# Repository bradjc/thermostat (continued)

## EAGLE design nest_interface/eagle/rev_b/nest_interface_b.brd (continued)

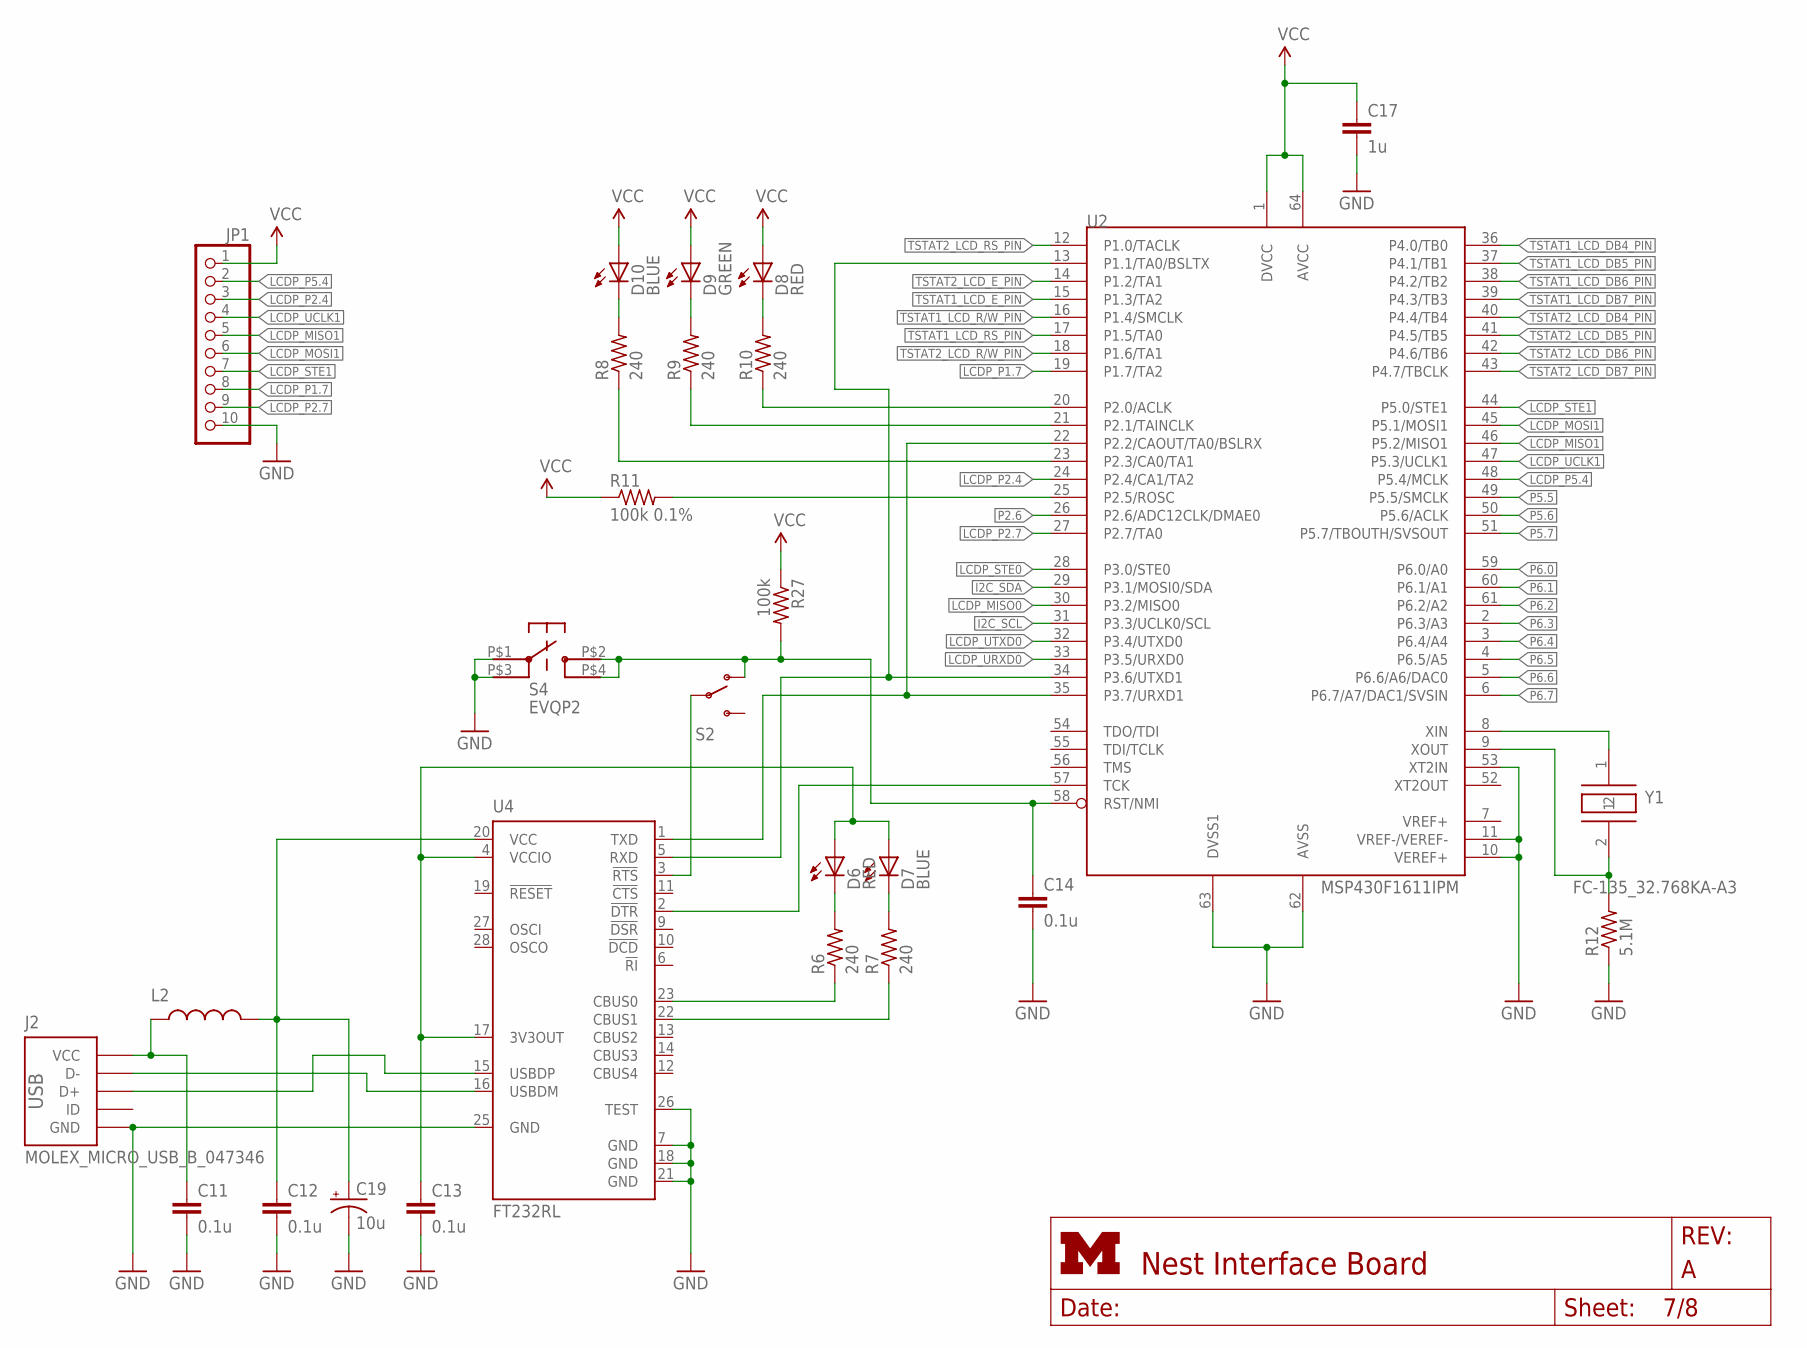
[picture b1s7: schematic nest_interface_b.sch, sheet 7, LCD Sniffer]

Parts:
C11, C12, C13, C14: 0.1u; C0603
C17: 1u; C0603
C19: 10u; EIA3216; DIGIKEY 478-1655-1-ND
D6, D8: RED; LED-0603
D7, D10: BLUE; LED-0603
D9: GREEN; LED-0603
J2: MOLEX_MICRO_USB_B_047346
JP1: PINHD-1X10; 1X10
L2: INDUCTOR0603; 0603; DIGIKEY 240-2373-1-ND
R6, R7, R8, R9, R10: 240; R0603
R11: 100k 0.1%; R0603
R12: 5.1M; R0603
R27: 100k; R0603
S2: SWITCH-SPSTPTH; SWITCH-SPDT; DIGIKEY EG1903-ND
S4: EVQP2; DIGIKEY P11084SCT-ND
U2: MSP430F1611IPM; PM/PAG64
U4: FT232RL; SSOP28; DIGIKEY 768-1007-1-ND
Y1: FC-135_32.768KA-A3; FC-135; DIGIKEY 535-9543-1-ND

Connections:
GND: C11.2, C12.2, C13.2, C14.2, C17.2, C19.C (-), J2.GND, JP1.10, R12.1, S4.P$1, S4.P$3, U2.10 (VEREF+), U2.11 (VREF-/VEREF-), U2.53 (XT2IN), U2.62 (AVSS), U2.63 (DVSS1), U4.7 (GND), U4.18 (GND), U4.21 (GND), U4.25 (GND), U4.26 (TEST); also elsewhere on the board
I2C_SCL: U2.31 (P3.3/UCLK0/SCL); also elsewhere on the board
I2C_SDA: U2.29 (P3.1/MOSI0/SDA); also elsewhere on the board
LCDP_MISO0: U2.30 (P3.2/MISO0)
LCDP_MISO1: JP1.5, U2.46 (P5.2/MISO1)
LCDP_MOSI1: JP1.6, U2.45 (P5.1/MOSI1)
LCDP_P1.7: JP1.8, U2.19 (P1.7/TA2)
LCDP_P2.3: R8.1, U2.23 (P2.3/CA0/TA1)
LCDP_P2.4: JP1.3, U2.24 (P2.4/CA1/TA2)
LCDP_P2.7: JP1.9, U2.27 (P2.7/TA0)
LCDP_P5.4: JP1.2, U2.48 (P5.4/MCLK)
LCDP_STE0: U2.28 (P3.0/STE0)
LCDP_STE1: JP1.7, U2.44 (P5.0/STE1)
LCDP_UART1RX: U2.22 (P2.2/CAOUT/TA0/BSLRX), U2.35 (P3.7/URXD1), U4.1 (TXD)
LCDP_UART1TX: U2.13 (P1.1/TA0/BSLTX), U2.34 (P3.6/UTXD1), U4.5 (RXD)
LCDP_UCLK1: JP1.4, U2.47 (P5.3/UCLK1)
LCDP_URXD0: U2.33 (P3.5/URXD0)
LCDP_UTXD0: U2.32 (P3.4/UTXD0)
unnamed: R10.1, U2.20 (P2.0/ACLK)
unnamed: D8.C, R10.2
unnamed: U2.8 (XIN), Y1.1
unnamed: C11.1, J2.VCC, L2.1
unnamed: J2.D-, U4.16 (USBDM)
unnamed: J2.D+, U4.15 (USBDP)
unnamed: C12.1, C19.A (+), L2.2, U4.20 (VCC)
unnamed: R6.1, U4.23 (CBUS0)
unnamed: R7.1, U4.22 (CBUS1)
unnamed: D6.C, R6.2
unnamed: D7.C, R7.2
unnamed: U2.57 (TCK), U4.2 (!DTR)
unnamed: C13.1, D6.A, D7.A, U4.4 (VCCIO), U4.17 (3V3OUT)
unnamed: R12.2, U2.9 (XOUT), Y1.2
unnamed: D9.C, R9.2
unnamed: R11.2, U2.25 (P2.5/ROSC)
unnamed: D10.C, R8.2
unnamed: R9.1, U2.21 (P2.1/TAINCLK)
P2.6: U2.26 (P2.6/ADC12CLK/DMAE0)
P5.5: U2.49 (P5.5/SMCLK)
P5.6: U2.50 (P5.6/ACLK)
P5.7: U2.51 (P5.7/TBOUTH/SVSOUT)
P6.0: U2.59 (P6.0/A0)
P6.1: U2.60 (P6.1/A1)
P6.2: U2.61 (P6.2/A2)
P6.3: U2.2 (P6.3/A3)
P6.4: U2.3 (P6.4/A4)
P6.5: U2.4 (P6.5/A5)
P6.6: U2.5 (P6.6/A6/DAC0)
P6.7: U2.6 (P6.7/A7/DAC1/SVSIN)
RST1: C14.1, R27.2, S2.1 (O), S4.P$2, S4.P$4, U2.58 (RST/NMI)
RST_USB1: S2.2, U4.3 (!RTS)
TSTAT1_LCD_DB4_PIN: U2.36 (P4.0/TB0); also elsewhere on the board
TSTAT1_LCD_DB5_PIN: U2.37 (P4.1/TB1); also elsewhere on the board
TSTAT1_LCD_DB6_PIN: U2.38 (P4.2/TB2); also elsewhere on the board
TSTAT1_LCD_DB7_PIN: U2.39 (P4.3/TB3); also elsewhere on the board
TSTAT1_LCD_E_PIN: U2.15 (P1.3/TA2); also elsewhere on the board
TSTAT1_LCD_R/W_PIN: U2.16 (P1.4/SMCLK); also elsewhere on the board
TSTAT1_LCD_RS_PIN: U2.17 (P1.5/TA0); also elsewhere on the board
TSTAT2_LCD_DB4_PIN: U2.40 (P4.4/TB4); also elsewhere on the board
TSTAT2_LCD_DB5_PIN: U2.41 (P4.5/TB5); also elsewhere on the board
TSTAT2_LCD_DB6_PIN: U2.42 (P4.6/TB6); also elsewhere on the board
TSTAT2_LCD_DB7_PIN: U2.43 (P4.7/TBCLK); also elsewhere on the board
TSTAT2_LCD_E_PIN: U2.14 (P1.2/TA1); also elsewhere on the board
TSTAT2_LCD_R/W_PIN: U2.18 (P1.6/TA1); also elsewhere on the board
TSTAT2_LCD_RS_PIN: U2.12 (P1.0/TACLK); also elsewhere on the board
VCC: C17.1, D8.A, D9.A, D10.A, JP1.1, R11.1, R27.1, U2.1 (DVCC), U2.64 (AVCC); also elsewhere on the board

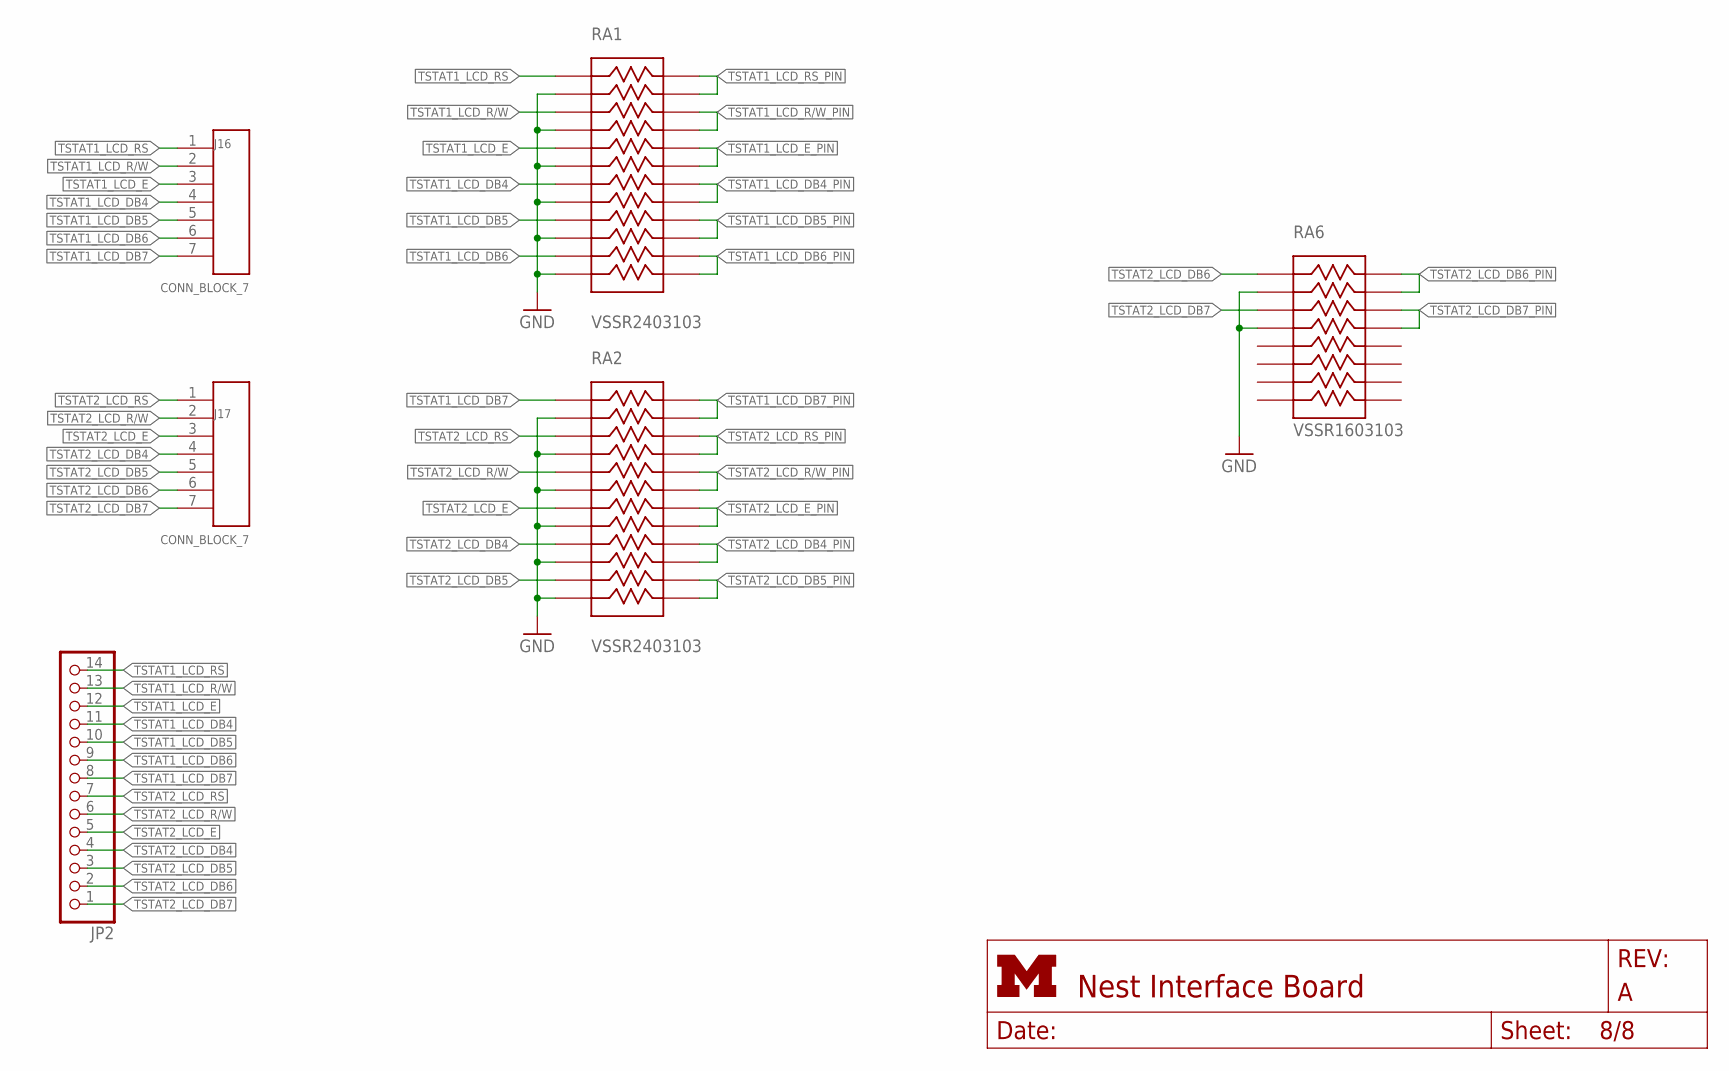
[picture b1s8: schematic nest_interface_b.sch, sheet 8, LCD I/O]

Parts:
J16, J17: CONN_BLOCK_7
JP2: PINHD-1X14; 1X14
RA1, RA2: VSSR2403103; LSSOP-24
RA6: VSSR1603103; LSSOP-16

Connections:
GND: RA1.2, RA1.4, RA1.6, RA1.8, RA1.10, RA1.12, RA2.2, RA2.4, RA2.6, RA2.8, RA2.10, RA2.12, RA6.2, RA6.4; also elsewhere on the board
TSTAT1_LCD_DB4: J16.4, JP2.11, RA1.7
TSTAT1_LCD_DB4_PIN: RA1.17, RA1.18; also elsewhere on the board
TSTAT1_LCD_DB5: J16.5, JP2.10, RA1.9
TSTAT1_LCD_DB5_PIN: RA1.15, RA1.16; also elsewhere on the board
TSTAT1_LCD_DB6: J16.6, JP2.9, RA1.11
TSTAT1_LCD_DB6_PIN: RA1.13, RA1.14; also elsewhere on the board
TSTAT1_LCD_DB7: J16.7, JP2.8, RA2.1
TSTAT1_LCD_DB7_PIN: RA2.23, RA2.24; also elsewhere on the board
TSTAT1_LCD_E: J16.3, JP2.12, RA1.5
TSTAT1_LCD_E_PIN: RA1.19, RA1.20; also elsewhere on the board
TSTAT1_LCD_R/W: J16.2, JP2.13, RA1.3
TSTAT1_LCD_R/W_PIN: RA1.21, RA1.22; also elsewhere on the board
TSTAT1_LCD_RS: J16.1, JP2.14, RA1.1
TSTAT1_LCD_RS_PIN: RA1.23, RA1.24; also elsewhere on the board
TSTAT2_LCD_DB4: J17.4, JP2.4, RA2.9
TSTAT2_LCD_DB4_PIN: RA2.15, RA2.16; also elsewhere on the board
TSTAT2_LCD_DB5: J17.5, JP2.3, RA2.11
TSTAT2_LCD_DB5_PIN: RA2.13, RA2.14; also elsewhere on the board
TSTAT2_LCD_DB6: J17.6, JP2.2, RA6.1
TSTAT2_LCD_DB6_PIN: RA6.15, RA6.16; also elsewhere on the board
TSTAT2_LCD_DB7: J17.7, JP2.1, RA6.3
TSTAT2_LCD_DB7_PIN: RA6.13, RA6.14; also elsewhere on the board
TSTAT2_LCD_E: J17.3, JP2.5, RA2.7
TSTAT2_LCD_E_PIN: RA2.17, RA2.18; also elsewhere on the board
TSTAT2_LCD_R/W: J17.2, JP2.6, RA2.5
TSTAT2_LCD_R/W_PIN: RA2.19, RA2.20; also elsewhere on the board
TSTAT2_LCD_RS: J17.1, JP2.7, RA2.3
TSTAT2_LCD_RS_PIN: RA2.21, RA2.22; also elsewhere on the board

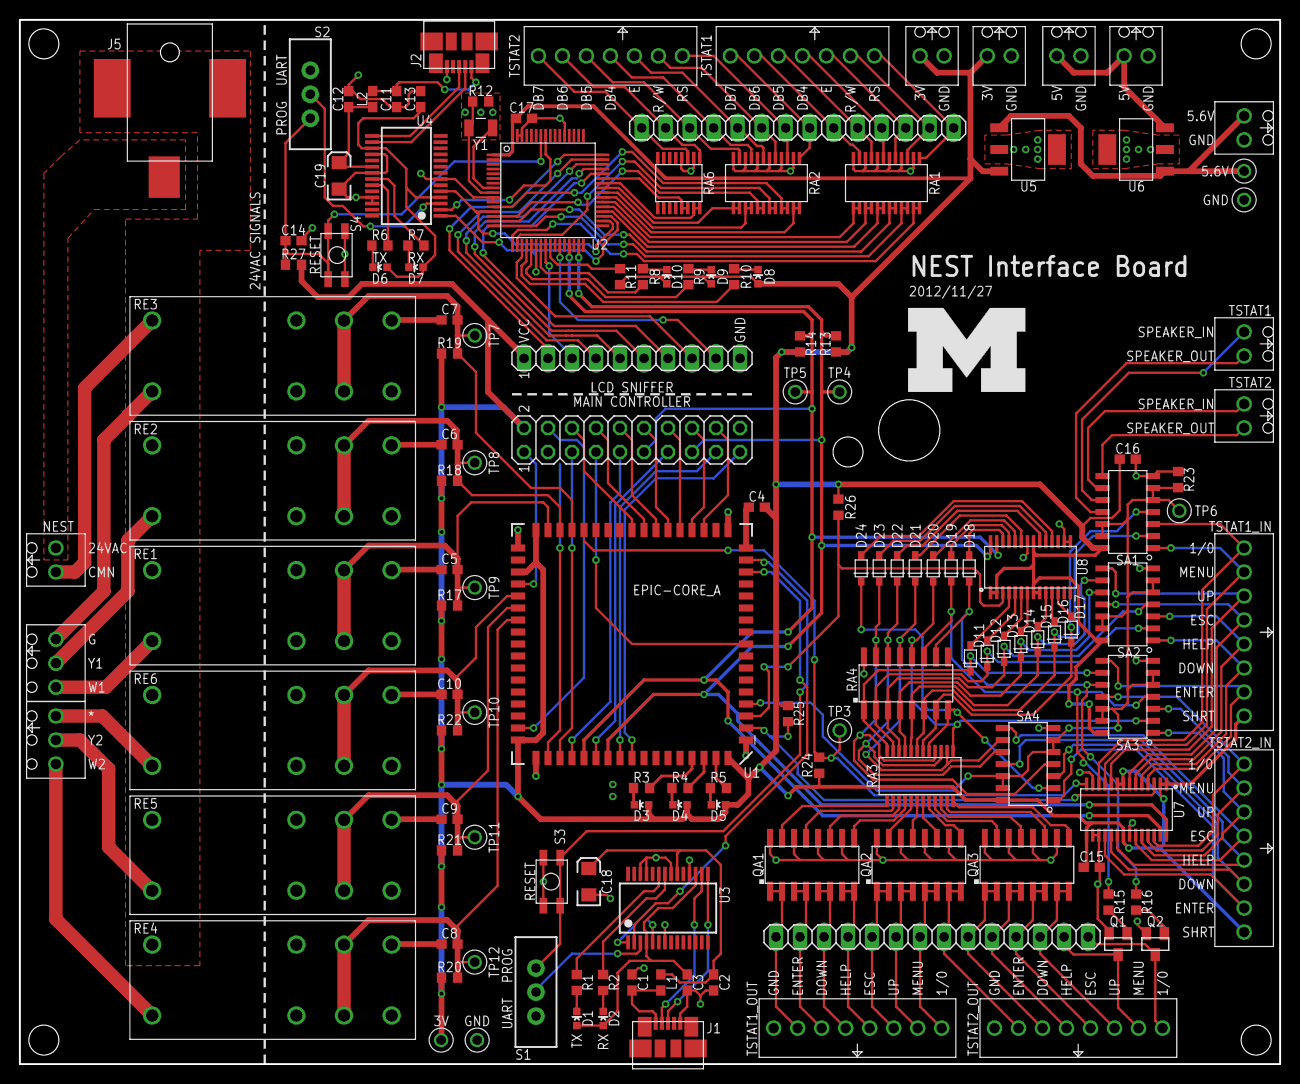
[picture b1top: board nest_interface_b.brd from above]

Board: 2 copper layers, 133.3 x 110.5 mm, 143 parts (0 on the bottom side), 194 nets.

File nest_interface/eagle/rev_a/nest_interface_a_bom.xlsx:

Quantity | Parts | Description | Part No. | Distributor | Package
1
Qty | Value | Device | Package | Parts | Description | DIGIKEY
16 | 0.1u | C-EUC0603 | C0603 | C1, C2, C3, C4, C5, C6, C7, C8, C9, C10, C11, C12, C13, C14, C18, C19 | CAPACITOR, European symbol
1 | 1u | C-EUC0603 | C0603 | C15 | CAPACITOR, European symbol
2 | 10u | CAP_POL1206 | EIA3216 | C16, C17 | Capacitor Polarized
10 |  | LED0603 | LED-0603 | D1, D2, D3, D4, D5, D6, D7, D8, D9, D10 | LEDs
2 | MOLEX_MICRO_USB_B_047346 | MOLEX_MICRO_USB_B_047346 | MOLEX_MICRO_USB_B_047346 | J1, J2 | Very tiny smd micro USB receptacle. | WM17141CT-ND
1 |  | PINHD-2X10 | 2X10 | J3 | PIN HEADER
1 |  | PINHD-1X8 | 1X08 | J4 | PIN HEADER
1 | PJ-036A-SMT | PJ-036A-SMT | PJ-0361-SMT | J5 | CONN PWR JACK 2.0X6.3MM SMT | CP-036APJCT-ND
8 | CONN_BLOCK_2 | CONN_BLOCK_2 | CONN_BLOCK_2 | J6, J7, J8, J9, J10, J11, J12, J13 | 2x 0.100 in screw terminal block | 277-1273-ND
2 | CONN_BLOCK_3 | CONN_BLOCK_3 | CONN_BLOCK_3 | J14, J15 | 3x 0.100 in screw terminal block | 277-1274-ND
2 | CONN_BLOCK_7 | CONN_BLOCK_7 | CONN_BLOCK_7 | J16, J17 | 7x 0.100 in screw terminal block | 277-1278-ND
4 | CONN_BLOCK_8 | CONN_BLOCK_8 | CONN_BLOCK_8 | J18, J19, J20, J21 | 8x 0.100 in screw terminal block | 277-1279-ND
2 |  | INDUCTOR0603 | L0603 | L1, L2 | Inductors
2 |  | TRANSISTOR_NPNSOT23 | SOT23 | Q1, Q2 | Transistor NPN | 568-1636-1-ND
3 | MMPQ2222A | MMPQ2222A | SOIC-16 | QA1, QA2, QA3 | 4 npn transistor array | MMPQ2222ACT-ND
4 | ALD1107 | ALD1107 | SOIC-14 | QA4, QA5, QA6, QA7 | 4x P-FET transistor chip | 1014-1015-ND
10 | 240 | R-US_R0603 | R0603 | R1, R2, R3, R4, R5, R6, R7, R8, R9, R10 | RESISTOR, American symbol
1 | 100k 0.1% | R-US_R0603 | R0603 | R11 | RESISTOR, American symbol
1 | 5.1M | R-US_R0603 | R0603 | R12 | RESISTOR, American symbol
4 | 10k | R-US_R0603 | R0603 | R13, R14, R15, R16 | RESISTOR, American symbol
11 | 100k | R-US_R0603 | R0603 | R17, R18, R19, R20, R21, R22, R23, R24, R25, R26, R27 | RESISTOR, American symbol
3 | VSSR2403103 | VSSR2403103 | LSSOP-24 | RA1, RA2, RA3 | 12x 10k resistor array | VSSR24-10K-JI-ND
2 | 766161104GP | 766161104GP | SOIC-16 | RA4, RA5 | 15x 100k resistor array bussed | 766-161-R100KP-ND
1 | VSSR1603103 | VSSR1603103 | LSSOP-16 | RA6 | RES ARRAY 10K OHM 8 RES 16-LSSOP | VSSR16-10K-JI-ND
6 | RT314524 | RT314524 | S0418-CA | RE1, RE2, RE3, RE4, RE5, RE6 | RELAY GEN PURPOSE SPDT 16A 24VAC | PB1238-ND
2 |  | SWITCH-SPSTPTH | SWITCH-SPDT | S1, S2 | SPST Switch | EG1903-ND
2 | EVQP2 | EVQP2 | EVQP2 | S3, S4
1 | EPIC-CORE_A | EPIC-CORE_A | EPIC-LCC68 | U1
1 | MSP430F1611IPM | MSP430F1611IPM | PM/PAG64 | U2
2 | FT232RL | FT232RL | SSOP28 | U3, U4 |  | 768-1007-1-ND
1 | MPC1825 | MPC1825 | SOT-223-3 | U5 | 3V 500mA LDO | MCP1825S-3002E/DB-ND
1 | TC1262 | TC1262 | SOT-223-3 | U6 | 5V 500mA LDO | TC1262-5.0VDB-ND
2 | PCA9575 | PCA9575 | TSSOP28 | U7, U8 | 16 channel I2C GPIO module. | 568-6647-1-ND
1 | FC-135_32.768KA-A3 | FC-135_32.768KA-A3 | FC-135 | Y1

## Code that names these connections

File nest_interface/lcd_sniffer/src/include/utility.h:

#ifndef __UTILITY_H__
#define __UTILITY_H__

#include <msp430.h>
#include <inttypes.h>
#include <stdio.h>


#define IDLE_CYCLES 4
// Used by the coding state machine to identify
// long and short pulses.
#define THRESHOLD 4
#define DELTAT 13


// Disables the watchdog timer
void util_disableWatchdog(void);
void util_boardInit(void);
void util_enableInterrupt(void);
void util_disableInterrupt(void);
void util_delayMs(uint16_t ms);

// DO NOT USE THIS FUNCTION
// unless you want to delay less than a MS
void util_delayCycles (uint16_t cycles);


#define LCD_SNIFF_I2C_ADDR 0x44

#define FALSE 0
#define TRUE  1

#define TSTAT1_LCD_RS_PORT  1
#define TSTAT1_LCD_RS_PIN   5
#define TSTAT1_LCD_E_PORT   1
#define TSTAT1_LCD_E_PIN    3
#define TSTAT1_LCD_RW_PORT  1
#define TSTAT1_LCD_RW_PIN   4
#define TSTAT1_LCD_DB4_PORT 4
#define TSTAT1_LCD_DB4_PIN  0
#define TSTAT1_LCD_DB5_PORT 4
#define TSTAT1_LCD_DB5_PIN  1
#define TSTAT1_LCD_DB6_PORT 4
#define TSTAT1_LCD_DB6_PIN  2
#define TSTAT1_LCD_DB7_PORT 4
#define TSTAT1_LCD_DB7_PIN  3

#define TSTAT2_LCD_RS_PORT  1
#define TSTAT2_LCD_RS_PIN   0
#define TSTAT2_LCD_E_PORT   1
#define TSTAT2_LCD_E_PIN    2
#define TSTAT2_LCD_RW_PORT  1
#define TSTAT2_LCD_RW_PIN   6
#define TSTAT2_LCD_DB4_PORT 4
#define TSTAT2_LCD_DB4_PIN  4
#define TSTAT2_LCD_DB5_PORT 4
#define TSTAT2_LCD_DB5_PIN  5
#define TSTAT2_LCD_DB6_PORT 4
#define TSTAT2_LCD_DB6_PIN  6
#define TSTAT2_LCD_DB7_PORT 4
#define TSTAT2_LCD_DB7_PIN  7

typedef uint8_t bool;

typedef enum {
	TSTAT1 = 0,
	TSTAT2 = 1,
} thermostat_e;


#endif

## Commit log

2012-03-27 wrote some code that extracts emails from mflicks list
2012-03-27 added html for mflicks email scraping
2012-04-07 added window display and svnstat stuff to the shed-extra git repo
2012-04-08 getting close to getting the new window display working
2012-04-08 Updated the window display page
2012-04-08 try this again
2012-04-08 couple tweaks to the new window display
2012-04-12 working on the git version of the window display
2012-04-12 got a decent start on the new line count
2012-04-12 graph pretty good for window disp 2
2012-04-15 graph and total lines work on the new window display
2012-04-25 adding printer query stuff
2012-04-25 printer script should work again
2012-04-25 twitter works again
2012-05-07 window display should work again
2012-05-07 working on window display 2 - changes made to get it to work on nuclear
2012-05-07 adding forgotten css file
2012-05-07 fixed sizing for windisplay2
2012-05-07 fixed plot colors
2012-05-07 file location fix
2012-05-07 cleaned up run_stats a tad
2012-09-28 nest interface board!!
2012-09-29 started routing the nest interface board
2012-09-29 routed the nest interface board
2012-09-29 added silkscreen to nest board
2012-10-02 tweaks to nest interface board
2012-10-02 adding more relays to the nest interface board in
    prep for v2
2012-10-03 added relays
2012-10-04 BETTER NEST
2012-10-04 added LCD datasheet
2012-10-05 saving nest i board
2012-10-06 started routing wow is that going to be tricky
2012-10-07 barebones lcd_sniffer folder, tup
    tup, as long as you put up with its bullshit, still comes out a little
    ahead of make
2012-10-07 cleaning up schematic/bom
2012-10-08 routing
2012-10-08 cleaned up the nib schematic
2012-10-08 updated bom
2012-10-08 more schematic updates
2012-10-08 MOAR ROUTING
2012-10-08 no airwires!!!!!
2012-10-09 labels cleaned up, looks good
2012-10-09 added decoupling caps, bom
2012-10-09 added board for keypad socket
2012-10-09 nest
2012-10-11 cleaned up two traces and started lcd code
2012-10-11 gpio code for lcd sniffer
2012-10-11 writing lcd code
2012-10-15 board changes, lcd code
2012-10-16 nib: before big keypad control change
2012-10-17 new ciruict routed - no airwires
2012-10-17 slight fixes
2012-10-17 board looks pretty nice
2012-10-18 working on the lcd sniffer
2012-10-20 board may actually be done
2012-10-20 ok a couple more fixes
2012-10-26 added nest interface stencil
2012-10-26 added nest stencil file
2012-10-26 fixed nest stencil pitch
2012-11-20 updated to rev b
    fixed the programmer for the lcd sniffer msp
2012-11-26 tinyos-ifying the nest code
2012-11-26 first pass on abstracting the nest tinyos code
    it compiles...
    now to see if it works
2012-11-26 Modular nest tinyos code works i think
2012-11-26 moved the nest interface code to its own module
2012-11-26 pins input and output work
    nest thingy works
2012-11-26 got a start on multi button press, doesnt seem to work yet
    probably need to change the set interface to something with a callback
2012-11-26 added set done to thermostat pins setting this should allow multiple button presses to work
2012-11-26 setting ignores
    updated multiple button module for nest board
2012-11-26 updated rev b of the nest board
2012-11-26 cleaned up some of the modules
2012-11-26 added a disable/enable interface to the input buttons so you dont get interrupts while setting output pins
2012-11-27 added ideas file for nib
2012-11-28 moved gpio interrupt to pin2.7
2012-12-18 working on new thermostat button architecture
2012-12-18 added clear funtion to thermgpio module
2012-12-18 renaming tstat layers
2012-12-18 renamed multi button
2012-12-18 much better architecture for nest output buttons
2012-12-18 set temp in tstat actions
2012-12-18 actions
2012-12-19 set temp action works on the surface
2012-12-19 compiles with code for talking to the lcd sniffer
2012-12-19 tested with everything except the i2c connection to the lcd sniffer
2012-12-19 added on off actions
2012-12-19 added a delay after each button press
2012-12-19 adding state fiel
2012-12-19 better wrapper for keypad enable disable
2012-12-19 cleaned up some warnings
2012-12-20 got my lcd code to compile
2012-12-20 fuck fuck fuck
2012-12-20 cools
2012-12-20 nest board
2012-12-21 new passthrough app
2013-01-03 Refactored button input code into the better generic style.
    Adding comments.
2013-01-03 Added comments to more of the nib code.
2013-01-14 ignores and a first pass on the tinyos cc2520rpi driver
    I've gotten the cc2520rpi driver to compile...but that's about it. I'm not sure all of the files I created will make it into the final version as I'm not quite sure what is handled in tinyos and what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
    Oh, and FUCK SVN.
2013-02-01 receiver stand 3d models
2013-02-01 moving so all my files are in one commit
2013-02-01 moving so all my files are in one commit
    Conflicts:
    nib/docs/TM162ad_lcd_module.pdf
    nib/docs/ffc_thru-hole_10pos_0.100in.pdf
    nib/docs/ideas.txt
    nib/docs/pca9575.pdf
    nib/eagle/keypad_socket/rev_a/keypad_socket_a.brd
2013-02-01 undoing...
2013-02-01 Got them in there
2013-02-01 adding nest apps
2013-02-01 nib compiles again
2013-02-01 import nib platform
2013-02-01 Adding in chips from shed
2013-02-04 tinyos app compiles
    Also added Duty Cycle app
2013-02-04 added tinyos build folders
2013-02-04 fixed indentation
2013-02-05 lcd sniffer seems to respond correctly
2013-02-05 i2c gpio actually get itited now
2013-02-05 updated app to blink led
2013-02-05 testing i2c
2013-02-07 Adding test for lcd
    Sends all lcd display bytes in udp packet
2013-02-09 reads lcd properly
    Code is an absolute mess, but I figured out the timing issues and the
    lcd sniffer can now read the lcd correctly. I need to add in the lcd
    status code and clean it up but this nest board is now really close to
    being real!
2013-02-10 better lcd reading
    Uses lcd_state file
2013-02-10 can successfully detect on/off
2013-02-10 can query for on/off
2013-02-10 can read temp, on/off, and humidity
2013-02-10 nest duty cycle works
    Need to change the lcd state code to work on lines and not screens. It's
    not uncommon for the lines on screen to become flipped.
2013-02-10 Changed lcd sniffer to handle lines
    No longer tries to maintain what is on the entire screen.
2013-02-11 working on nest duty cycle
    It works better, but something is still wrong where actionDone is
    getting signaled in the top level app, every 5 seconds when the lcd test
    code is sending the status.
2013-02-12 fixed enable/disable for input pins
    Now you can disable a single bank of input pins
2013-02-12 Fixed I2C bug where .granted() was problematic
    The state machine was getting triggered when I didn't expect it, causing
    upper layers to get signaled spuriously. I still think there is a bug in
    the msp i2c code or in nesc, because i don't know why .granted() was
    getting called when the i2c_state == I2C_ST_SET_PIN2.
2013-02-13 duty cycle test seems to be working
2013-02-14 State machine improvement
    Added a null state just in case any weirdness happens
2013-02-14 removed old code
2013-02-18 added timer to periodically reconfigure gpio ext
    Every minute reprograms the gpio extenders
2013-02-18 Disabled both keypads
2014-01-16 folder tree correct
2014-01-16 new doc for nib
